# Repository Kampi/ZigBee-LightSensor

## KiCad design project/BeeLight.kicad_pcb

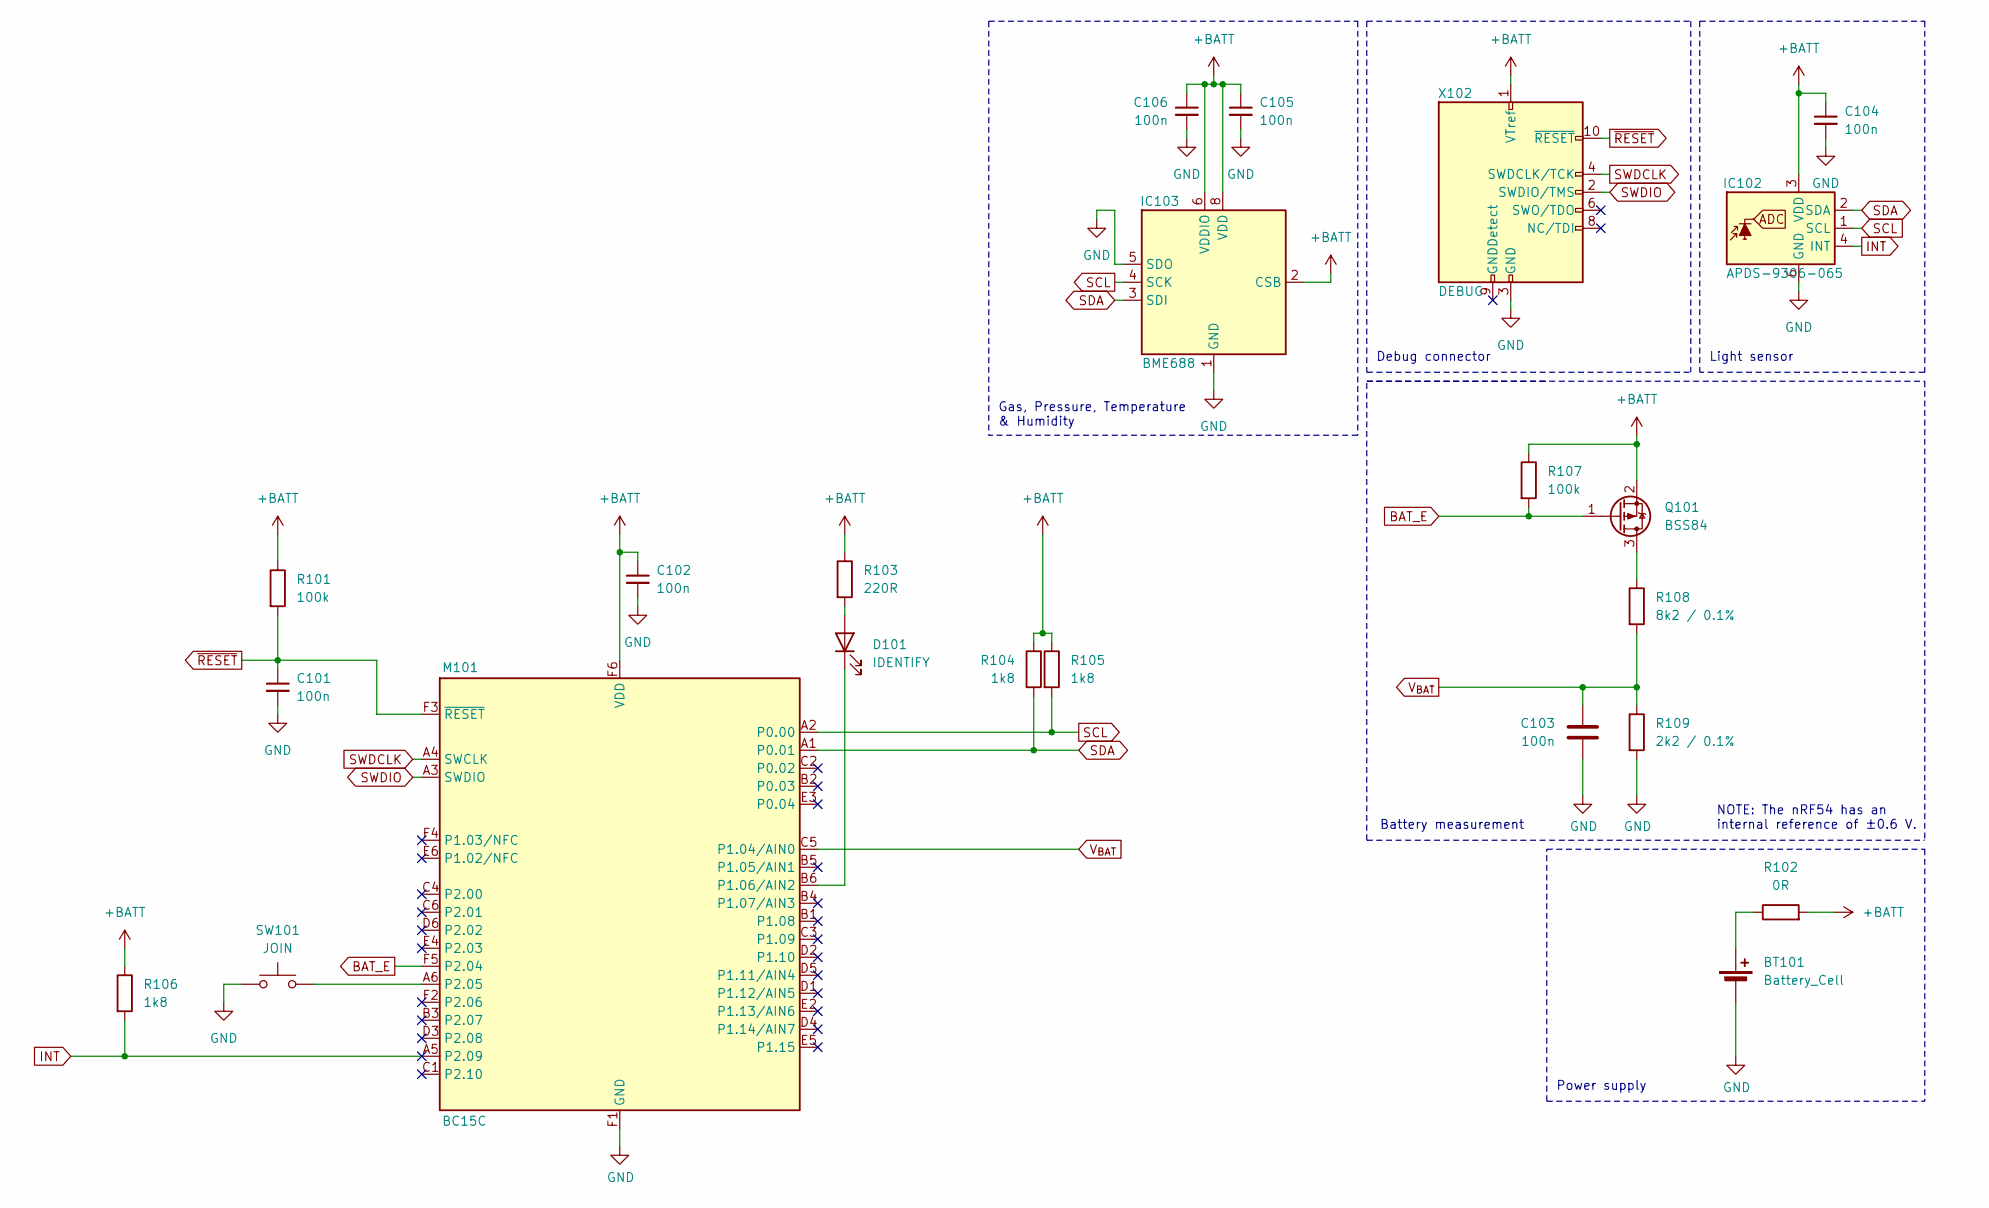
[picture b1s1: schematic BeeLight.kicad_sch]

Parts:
BT101: Battery_Cell; 3002; mouser# 534-3002
C101, C102, C103, C104, C105, C106: 100n; C_0402_1005Metric_Pad0.74x0.62mm_HandSolder; mouser# 581-04025C104KAT4A
D101: IDENTIFY; LED_0805_2012Metric_Pad1.15x1.40mm_HandSolder; mouser# 630-HSMQ-C170-T0000
IC102: APDS-9306-065; Broadcom_DFN-6_2x2mm_P0.65mm; mouser# 630-APDS-9306-065
IC103: BME688; Bosch_LGA-8_3x3mm_P0.8mm_ClockwisePinNumbering; mouser# 262-BME688
M101: BC15C; mouser# 308-BM15C
Q101: BSS84; SOT-23-3; mouser# 512-BSS84
R101, R107: 100k; R_0402_1005Metric_Pad0.72x0.64mm_HandSolder; mouser# 603-RC0402FR-07100KL
R102: 0R; R_0805_2012Metric_Pad1.20x1.40mm_HandSolder; mouser# 652-CR0805AJ/-000EAS
R103: 220R; R_0402_1005Metric_Pad0.72x0.64mm_HandSolder; mouser# 652-CR0402-JW-221GLF
R104, R105, R106: 1k8; R_0402_1005Metric_Pad0.72x0.64mm_HandSolder; mouser# 603-RC0402FR-071K8L
R108: 8k2 / 0.1%; R_0402_1005Metric_Pad0.72x0.64mm_HandSolder; mouser# 603-RT0402BRD078K2L
R109: 2k2 / 0.1%; R_0402_1005Metric_Pad0.72x0.64mm_HandSolder; mouser# 603-RT0402BRD072K2L
SW101: JOIN; WS-TASV-6x6; mouser# 710-430182095816
X102: DEBUG; PinHeader_2x05_P1.27mm_Vertical; mouser# 200-SHF-105-01-L-D-TH-TR

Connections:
+BATT: C102.1, C104.1, C105.1, C106.1, IC102.3 (VDD), IC103.2 (CSB), IC103.6 (VDDIO), IC103.8 (VDD), M101.F6 (VDD), Q101.2 (S), R101.1, R102.2, R103.1, R104.1, R105.1, R106.1, R107.1, X102.1 (VTref)
BAT_E: M101.F5 (P2.04), Q101.1 (G), R107.2
GND: BT101.2 (-), C101.2, C102.2, C103.2, C104.2, C105.2, C106.2, IC102.6 (GND), IC103.1 (GND), IC103.5 (SDO), IC103.7 (GND), M101.E1 (GND), M101.F1 (GND), R109.2, SW101.1, X102.3 (GND), X102.5 (GND)
INT: IC102.4 (INT), M101.A5 (P2.09), R106.2
unnamed: BT101.1 (+), R102.1
unnamed: D101.2 (A), R103.2
unnamed: D101.1 (K), M101.B6 (P1.06/AIN2)
unnamed: M101.A6 (P2.05), SW101.2
unnamed: Q101.3 (D), R108.1
SCL: IC102.1 (SCL), IC103.4 (SCK), M101.A2 (P0.00), R105.2
SDA: IC102.2 (SDA), IC103.3 (SDI), M101.A1 (P0.01), R104.2
SWDCLK: M101.A4 (SWCLK), X102.4 (SWDCLK/TCK)
SWDIO: M101.A3 (SWDIO), X102.2 (SWDIO/TMS)
V_{BAT}: C103.1, M101.C5 (P1.04/AIN0), R108.2, R109.1
~RESET: C101.1, M101.F3 (~RESET), R101.2, X102.10 (~RESET)

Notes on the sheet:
Debug connector
Gas, Pressure, Temperature & Humidity
NOTE: The nRF54 has an internal reference of ±0.6 V.
Light sensor
Battery measurement
Power supply

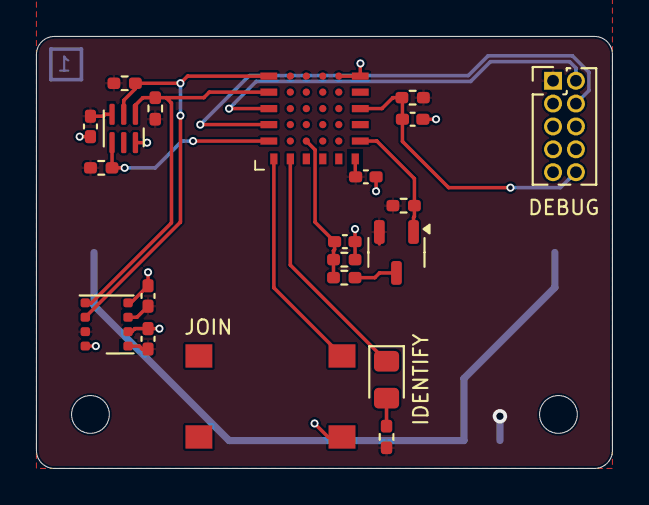
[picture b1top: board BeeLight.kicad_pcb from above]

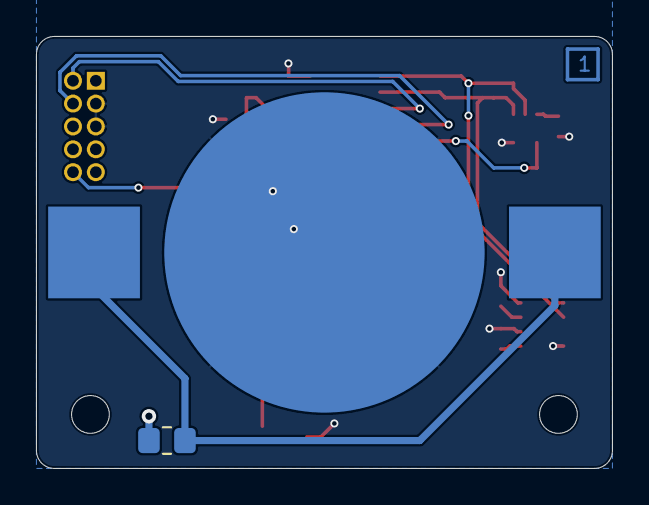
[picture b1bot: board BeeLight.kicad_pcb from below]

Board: 2 copper layers, 32.0 x 24.0 mm, 23 parts (2 on the bottom side), 15 nets.

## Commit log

2025-01-14 Replace nRF53 with nRF54L
2025-01-20 Add BME688 to overlay
